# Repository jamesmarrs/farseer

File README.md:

# farseer

In-car race telemetry module: GPS uplink over UDP via Quectel BG95-M3, with a
low-volume server downlink.

## Bench wiring

See [docs/bench-wiring.md](docs/bench-wiring.md) for Curiosity Nano + Sixfab
Cellular IoT HAT connections, power rails, and bring-up checklist.

## Custom board

**The KiCad project is the single source of truth for the circuit** —
schematic, nets, reference designators, values, footprints, and MPNs. Open it
with:

```bash
open ki_cad_project/farseer/farseer.kicad_pro
```

Export the rendered schematic PDF and the BOM CSV (into `docs/generated/`,
machine-generated — never hand-edit) with:

```bash
./scripts/export_kicad.sh
```

The design *rationale* — datasheet citations, sizing math, traps, and
trade-offs the schematic cannot carry — lives in `docs/`, one document per
block: [MCU](docs/mcu-support-circuit.md),
[cellular](docs/cellular-support-circuit.md),
[GNSS](docs/gnss-support-circuit.md),
[power](docs/power-support-circuit.md), and
[interconnect](docs/interconnect-and-pin-budget.md) where the pin budget is
reconciled against the 48-pin PPS tables. Off-board parts (antennas, pigtail,
SIM) and cost estimates are in [docs/procurement.md](docs/procurement.md).
Pre-KiCad drawings and BOMs are retained in `docs/_archive/` for history only
and must not be treated as authoritative.

It carries no on-board debugger, so the Curiosity Nano's one-cable-does-everything
arrangement splits in two:

| | Bench (Curiosity Nano) | Custom board |
|---|---|---|
| Program + debug | Micro-USB to the on-board ATSAMD21 | **PICkit 5** on `J_icsp`, a 6-pin ICSP header |
| 115200 console | Same cable, debugger's CDC | **USB-C** on `J_dbg`, via a CP2102N bridge |

USB on the custom board is **data only** — it never powers the board, and the
PICkit must not be asked to power the target either.

## Server UDP tunnel (LocalXpose)

The module sends its telemetry datagrams over UDP to `BG95_SERVER_HOST` /
`BG95_SERVER_PORT` (defined in `bg95.h`). During development that destination is
a [LocalXpose](https://localxpose.io/) (`loclx`) UDP tunnel that forwards public
traffic to a listener on the dev machine.

### One-time setup

```bash
loclx account login                       # authenticate (UDP forwarding needs a paid plan)
loclx endpoint reserve --port 59128 --region us   # reserve us.loclx.io:59128 (once)
```

### Run the tunnel

Start the tunnel BEFORE powering the module, and forward to the same port your
server binds:

```bash
loclx tunnel udp --reserved-endpoint us.loclx.io:59128 --to 127.0.0.1:9000
```

### Gotchas (learned the hard way)

- **Use `127.0.0.1`, never `localhost`, in `--to`.** With `--to localhost:9000`
  loclx does not forward: `localhost` can resolve to IPv6 `::1` while the server
  binds IPv4, so tunneled packets are silently dropped even though the tunnel
  shows "running". Always use the IP literal, e.g. `--to 127.0.0.1:9000`.
- **Keep the port in sync.** The reserved-endpoint port, the module's
  `BG95_SERVER_PORT` in `bg95.h`, and your server's bind port (the `--to` port)
  must all agree. The reserved endpoint's public port and the local `--to` port
  do NOT have to match each other, but the module must target the public port.
- **`--to` port must match the server's bind port**, and the server must listen
  on that UDP port (e.g. `nc -u -l 9000` for a quick stand-in).
- **UDP forwarding is a paid `loclx` feature.** On a free plan the tunnel can
  appear up but never forward UDP.
- **`SEND OK` from the BG95 only means the module handed the datagram to the
  network** — UDP has no delivery ack, so it does not confirm the server (or
  tunnel) received anything.

### Verify the public path

Independently of the module, send a probe to the public endpoint and watch the
server (or a `nc -u -l <port>` stand-in) for it:

```bash
echo "probe" | nc -u -w1 us.loclx.io 59128
```

If the probe lands, the tunnel is good and any remaining delivery gap is on the
module egress side (e.g. BG95 DNS resolution of the host). If it does not land,
the tunnel/endpoint/port/plan is the problem — no firmware change will help.

## Structure

| Path                       | Purpose                                                                                                                             |
|----------------------------|-------------------------------------------------------------------------------------------------------------------------------------|
| _build                     | The [CMake build tree](https://cmake.org/cmake/help/latest/manual/cmake.1.html#introduction-to-cmake-buildsystems), can be deleted. |
| cmake                      | Generated [CMake](https://cmake.org/) files. May be deleted if user.cmake has not been added                                        |
| .vscode                    | See [VSCode](https://code.visualstudio.com/docs/getstarted/settings)                                                                |
| .vscode/settings.json      | Workspace specific settings                                                                                                         |
| .vscode/farseer.mplab.json | The MPLAB project file, should not be deleted                                                                                       |
| out                        | Final build artifacts                                                                                                               |

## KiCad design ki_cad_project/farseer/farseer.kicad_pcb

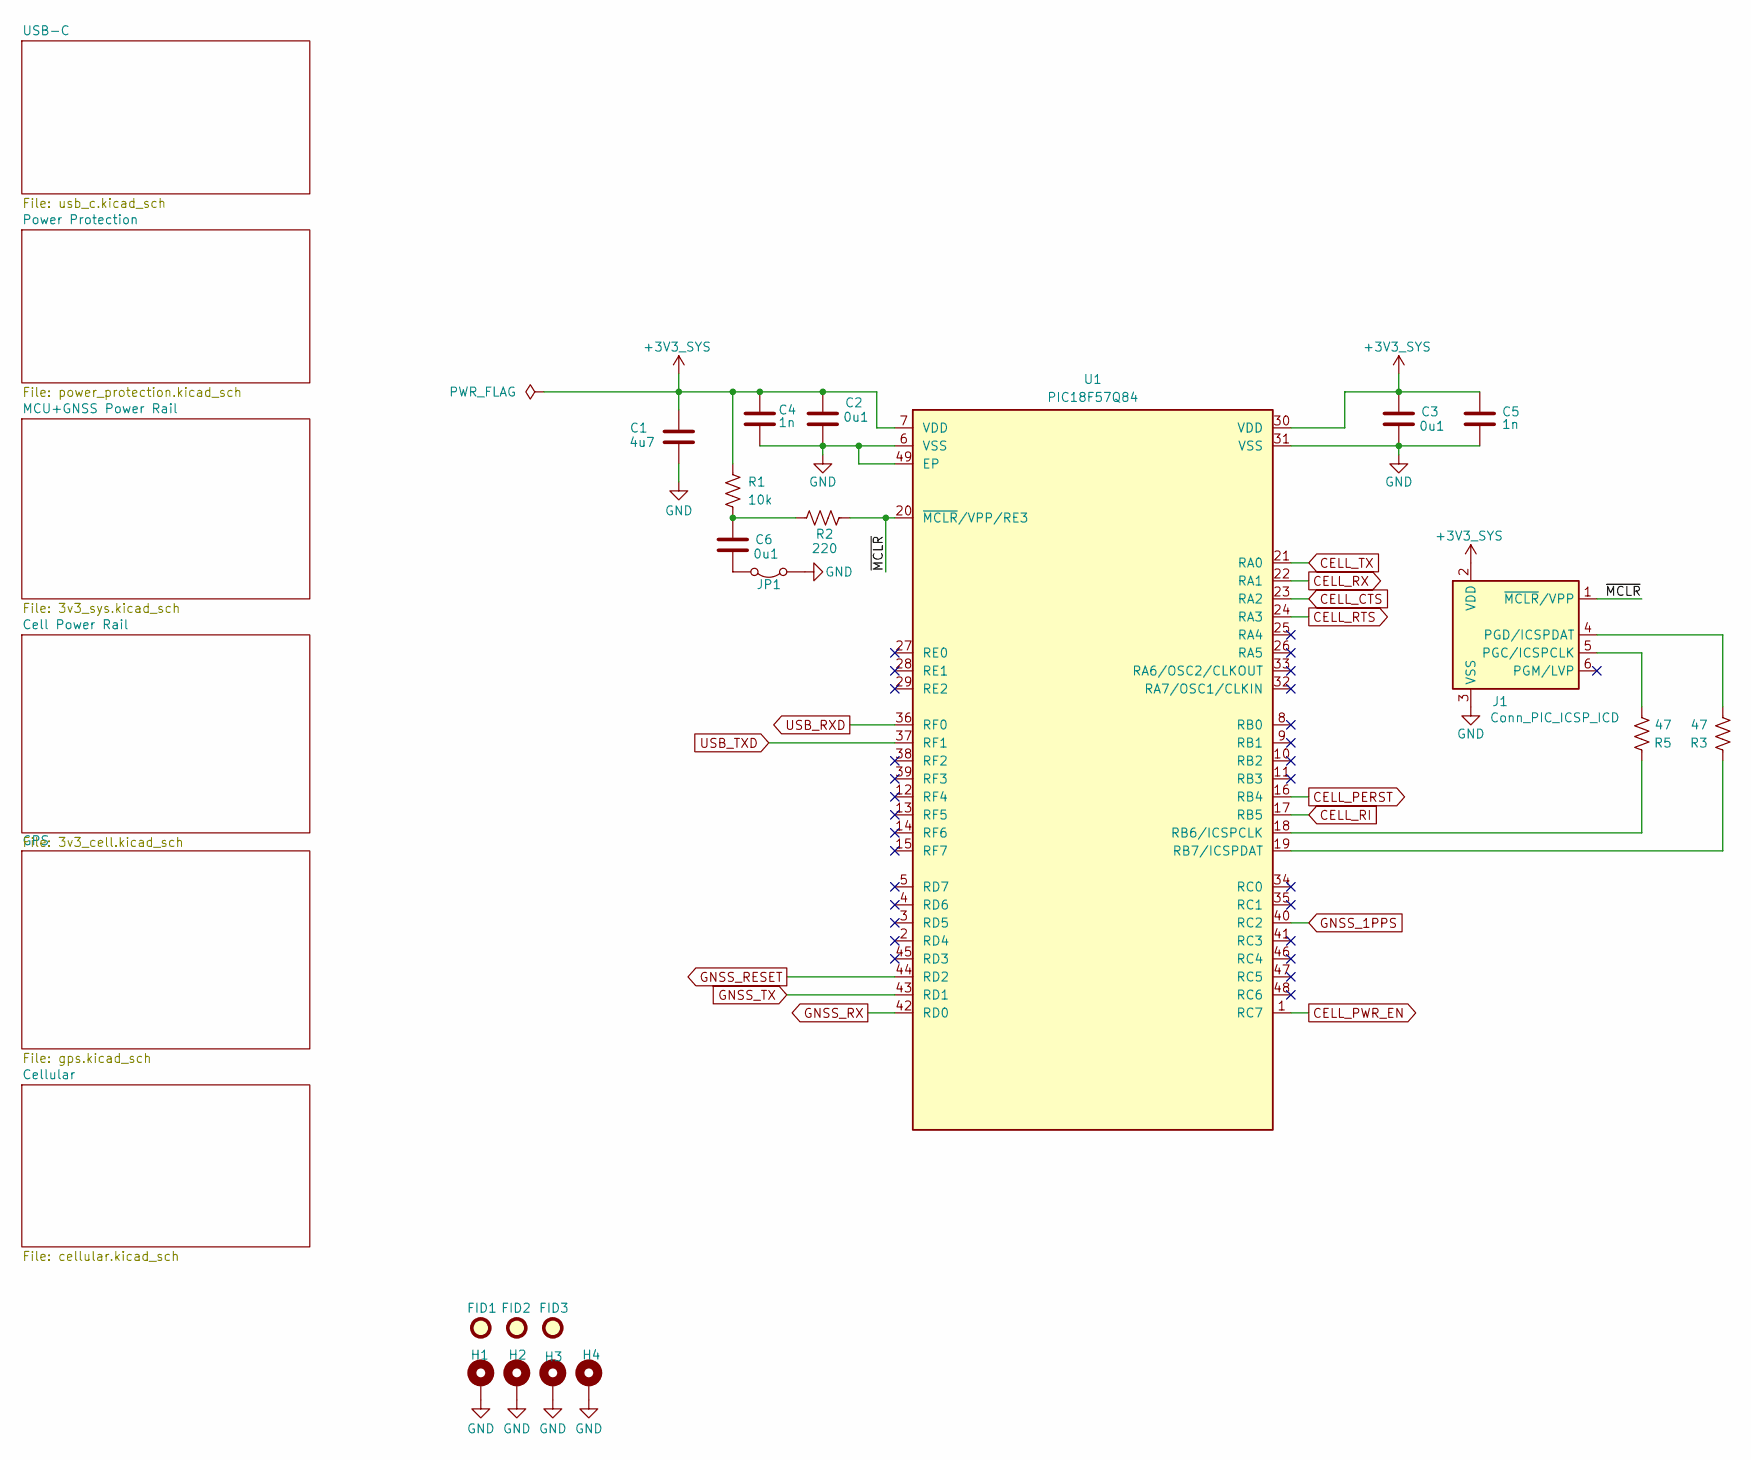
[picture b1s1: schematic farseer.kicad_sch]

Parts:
C1: 4u7; C_0805_2012Metric; MPN GCM21BR71C475KA73L
C2, C3, C6: 0u1; C_0402_1005Metric; MPN GCM155R71E104KE02D
C4, C5: 1n; C_0402_1005Metric; MPN GCM155R71H102KA37D
FID1, FID2, FID3: Fiducial; Fiducial_1mm_Mask2mm
H1, H2, H3, H4: MountingHole; MountingHole_3.2mm_M3_Pad_Via
J1: Conn_PIC_ICSP_ICD; PinHeader_1x06_P2.54mm_Vertical; MPN 61300611021
JP1: PinHeader_1x02_P2.54mm_Vertical; MPN 61300211121
R1: 10k; R_0603_1608Metric; MPN AC0603FR-0710KL
R2: 220; R_0603_1608Metric; MPN AC0603FR-07220RL
R3, R5: 47; R_0603_1608Metric; MPN AC0603FR-0747RL
U1: PIC18F57Q84; TQFP-48-1EP_7x7mm_P0.5mm_EP3.5x3.5mm_ThermalVias; MPN PIC18F57Q84-I/PT; DigikeyPN 150-PIC18F57Q84-I/PT-ND

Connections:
+3V3_SYS: C1.2, C2.1, C3.1, C4.1, C5.1, J1.2 (VDD), R1.1, U1.7 (VDD), U1.30 (VDD); also elsewhere on the board
/~MCLR: J1.1 (~MCLR/VPP), R2.2, U1.20 (~MCLR/VPP/RE3)
CELL_CTS: U1.23 (RA2); also elsewhere on the board
CELL_PERST: U1.16 (RB4); also elsewhere on the board
CELL_PWR_EN: U1.1 (RC7); also elsewhere on the board
CELL_RI: U1.17 (RB5); also elsewhere on the board
CELL_RTS: U1.24 (RA3); also elsewhere on the board
CELL_RX: U1.22 (RA1); also elsewhere on the board
CELL_TX: U1.21 (RA0); also elsewhere on the board
GND: C1.1, C2.2, C3.2, C4.2, C5.2, H1.1 (1_1), H2.1 (1_1), H3.1 (1_1), H4.1 (1_1), J1.3 (VSS), JP1.2 (B), U1.6 (VSS), U1.31 (VSS), U1.49 (EP); also elsewhere on the board
GNSS_1PPS: U1.40 (RC2); also elsewhere on the board
GNSS_RESET: U1.44 (RD2); also elsewhere on the board
GNSS_RX: U1.42 (RD0); also elsewhere on the board
GNSS_TX: U1.43 (RD1); also elsewhere on the board
unnamed: C6.1, R1.2, R2.1
unnamed: J1.5 (PGC/ICSPCLK), R5.2
unnamed: J1.4 (PGD/ICSPDAT), R3.2
unnamed: C6.2, JP1.1 (A)
unnamed: R5.1, U1.18 (RB6/ICSPCLK)
unnamed: R3.1, U1.19 (RB7/ICSPDAT)
USB_RXD: U1.36 (RF0); also elsewhere on the board
USB_TXD: U1.37 (RF1); also elsewhere on the board

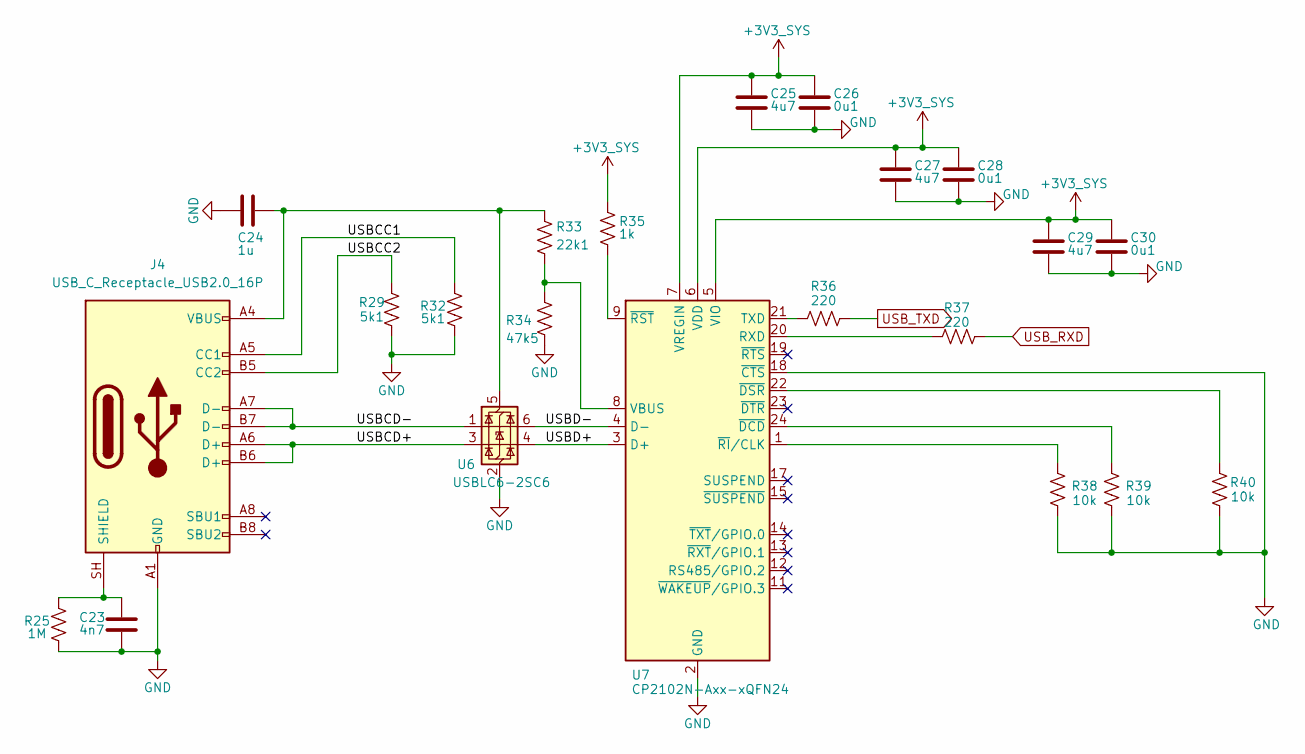
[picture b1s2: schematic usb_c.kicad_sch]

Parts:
C23: 4n7; C_1206_3216Metric; MPN C1206C472KGRACAUTO
C24: 1u; C_0402_1005Metric; MPN GCM155R71C105KA55D
C25, C27, C29: 4u7; C_0603_1608Metric; MPN GRT188C71C475KE13D
C26, C28, C30: 0u1; C_0402_1005Metric; MPN GCM155R71E104KE02D
J4: USB_C_Receptacle_USB2.0_16P; USB_C_Receptacle_GCT_USB4105-xx-A_16P_TopMnt_Horizontal; MPN USB4105-GF-A
R25: 1M; R_0603_1608Metric; MPN AC0603FR-071ML
R29, R32: 5k1; R_0603_1608Metric; MPN AC0603FR-075K1L
R33: 22k1; R_0603_1608Metric; MPN AC0603FR-0722K1L
R34: 47k5; R_0603_1608Metric; MPN AC0603FR-0747K5L
R35: 1k; R_0603_1608Metric; MPN AC0603FR-071KL
R36, R37: 220; R_0603_1608Metric; MPN AC0603FR-07220RL
R38, R39, R40: 10k; R_0603_1608Metric; MPN AC0603FR-0710KL
U6: USBLC6-2SC6; SOT-23-6; MPN USBLC6-2SC6Y
U7: CP2102N-Axx-xQFN24; QFN-24-1EP_4x4mm_P0.5mm_EP2.6x2.6mm; MPN CP2102N-A02-GQFN24

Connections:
+3V3_SYS: C25.1, C26.1, C27.1, C28.1, C29.1, C30.1, R35.2, U7.5 (VIO), U7.6 (VDD), U7.7 (VREGIN); also elsewhere on the board
/USB-C/USBCC1: J4.A5 (CC1), R32.2
/USB-C/USBCC2: J4.B5 (CC2), R29.1
/USB-C/USBCD+: J4.A6 (D+), J4.B6 (D+), U6.3 (I/O2)
/USB-C/USBCD-: J4.A7 (D-), J4.B7 (D-), U6.1 (I/O1)
/USB-C/USBD+: U6.4 (I/O2), U7.3 (D+)
/USB-C/USBD-: U6.6 (I/O1), U7.4 (D-)
GND: C23.2, C24.2, C25.2, C26.2, C27.2, C28.2, C29.2, C30.2, J4.A1 (GND), J4.A12 (GND), J4.B1 (GND), J4.B12 (GND), R25.1, R29.2, R32.1, R34.1, R38.1, R39.1, R40.1, U6.2 (GND), U7.2 (GND), U7.18 (~CTS), U7.25 (GND); also elsewhere on the board
unnamed: C23.1, J4.SH (SHIELD), R25.2
unnamed: C24.1, J4.A4 (VBUS), J4.A9 (VBUS), J4.B4 (VBUS), J4.B9 (VBUS), R33.1, U6.5 (VBUS)
unnamed: R37.2, U7.20 (RXD)
unnamed: R36.1, U7.21 (TXD)
unnamed: R33.2, R34.2, U7.8 (VBUS)
unnamed: R39.2, U7.24 (~DCD)
unnamed: R40.2, U7.22 (~DSR)
unnamed: R38.2, U7.1 (~RI/CLK)
unnamed: R35.1, U7.9 (~RST)
USB_RXD: R37.1; also elsewhere on the board
USB_TXD: R36.2; also elsewhere on the board

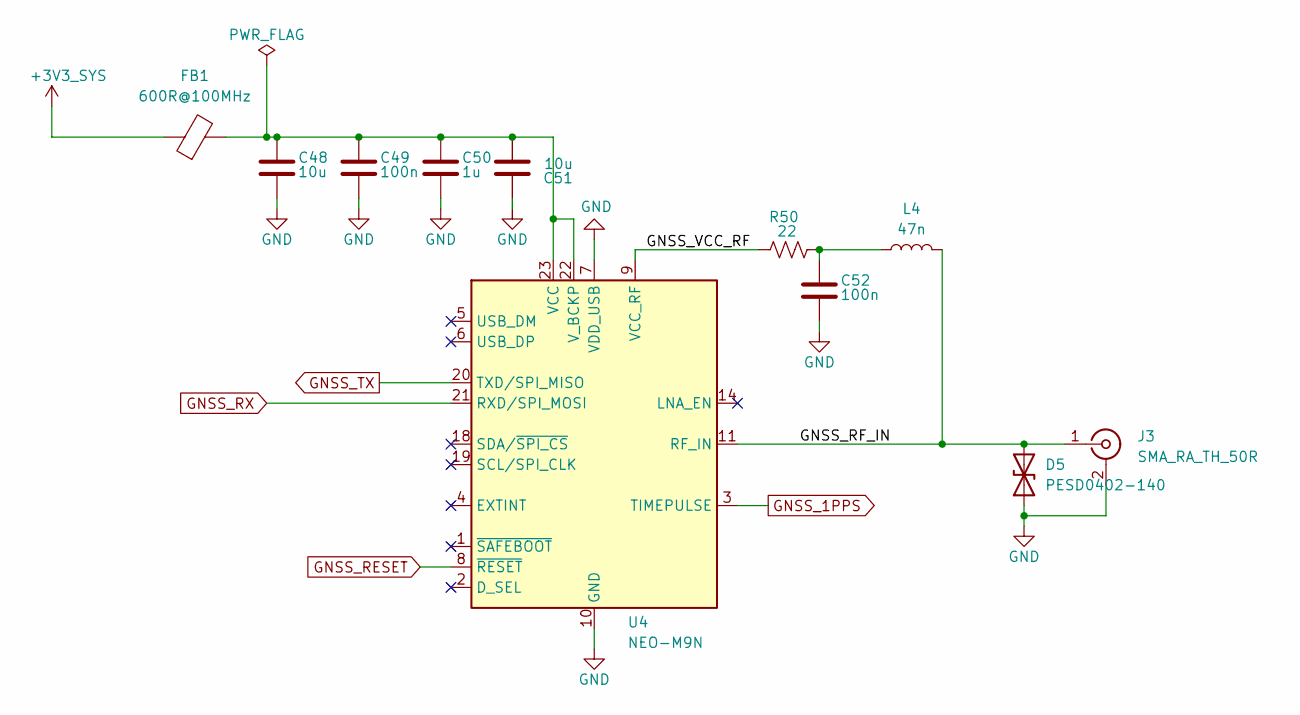
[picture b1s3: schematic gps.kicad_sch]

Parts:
C48, C51: 10u; C_0805_2012Metric; MPN GCM21BR71C106KE22L
C49, C52: 100n; C_0402_1005Metric; MPN GCM155R71C104KA55D
C50: 1u; C_0603_1608Metric; MPN GCM188R71C105KA64D
D5: PESD0402-140; D_0402_1005Metric_PESD0402-140; MPN PESD0402-140
FB1: 600R@100MHz; L_0603_1608Metric; MPN BLM18KG601SZ1D
J3: SMA_RA_TH_50R; SMA_Amphenol_901-143_Horizontal; MPN 132136; DigikeyPN ACX1232-ND
L4: 47n; L_0603_1608Metric; MPN LQW18AN47NG00D
R50: 22; R_0805_2012Metric; MPN ERJ-P06J220V
U4: NEO-M9N; ublox_NEO-M9N-00B; MPN NEO-M9N-00B

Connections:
+3V3_SYS: FB1.1; also elsewhere on the board
/GPS/GNSS_RF_IN: D5.2 (A2), J3.1 (In), L4.2, U4.11 (RF_IN)
/GPS/GNSS_VCC_RF: R50.1, U4.9 (VCC_RF)
GND: C48.2, C49.2, C50.2, C51.1, C52.2, D5.1 (A1), J3.2 (Ext), U4.7 (VDD_USB), U4.10 (GND), U4.12 (GND), U4.13 (GND), U4.24 (GND); also elsewhere on the board
GNSS_1PPS: U4.3 (TIMEPULSE); also elsewhere on the board
GNSS_RESET: U4.8 (~RESET); also elsewhere on the board
GNSS_RX: U4.21 (RXD/SPI_MOSI); also elsewhere on the board
GNSS_TX: U4.20 (TXD/SPI_MISO); also elsewhere on the board
unnamed: C52.1, L4.1, R50.2
unnamed: C48.1, C49.1, C50.1, C51.2, FB1.2, U4.22 (V_BCKP), U4.23 (VCC)

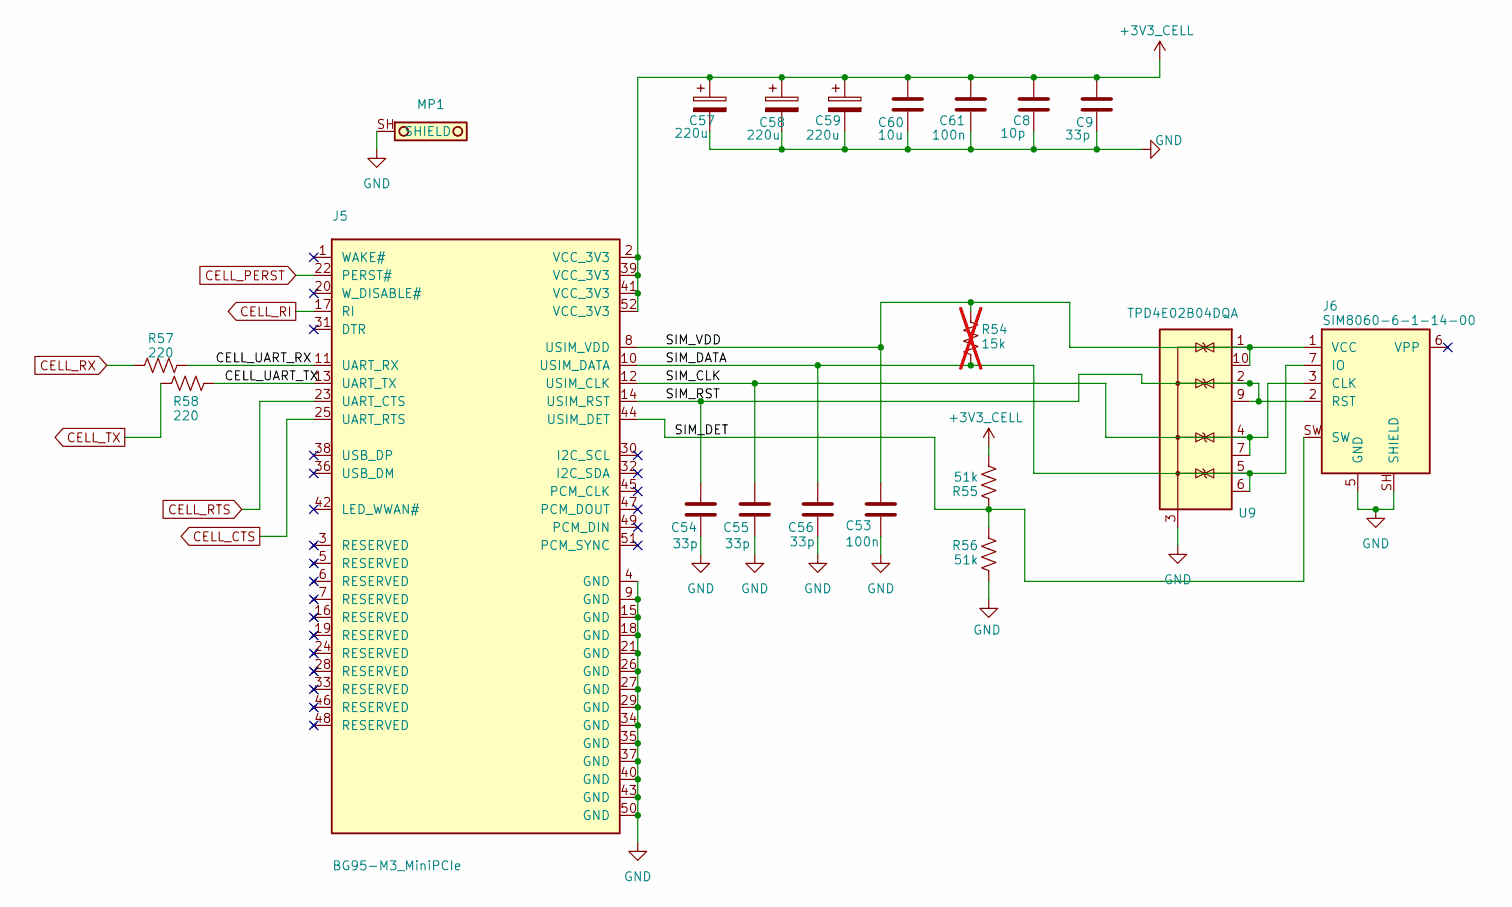
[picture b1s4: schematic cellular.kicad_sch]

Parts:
C8: 10p; C_0402_1005Metric; MPN GCM1555C1H100JA16D
C9, C54, C55, C56: 33p; C_0402_1005Metric; MPN GCM1555C1H330JA16D
C53, C61: 100n; C_0402_1005Metric; MPN GCM155R71C104KA55D
C57, C58, C59: 220u; CP_EIA-7343-31_Kemet-D; MPN T525D227M006ATE025
C60: 10u; C_0805_2012Metric; MPN GCM21BR71C106KE22L
J5: BG95-M3_MiniPCIe; Molex_67910-5700_MiniPCIe; MPN 679105700
J6: SIM8060-6-1-14-00; nanoSIM_GCT_SIM8060-6-1-14-00; MPN SIM8060-6-1-14-00-A
MP1: MiniPCIe_Latch; Molex_48099-5701_MiniPCIe_Latch; MPN 48099-5701
R54: 15k; R_0402_1005Metric; MPN AC0402FR-0715KL; not fitted
R55, R56: 51k; R_0402_1005Metric; MPN AC0402FR-0751KL
R57, R58: 220; R_0603_1608Metric; MPN AC0603FR-07220RL
U9: TPD4E02B04DQA; USON-10_2.5x1.0mm_P0.5mm; MPN TPD4E02B04DQAR

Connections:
+3V3_CELL: C8.1, C9.1, C57.1, C58.1, C59.1, C60.1, C61.1, J5.2 (VCC_3V3), J5.39 (VCC_3V3), J5.41 (VCC_3V3), J5.52 (VCC_3V3), R55.2; also elsewhere on the board
/Cellular/CELL_UART_RX: J5.11 (UART_RX), R57.2
/Cellular/CELL_UART_TX: J5.13 (UART_TX), R58.2
/Cellular/SIM_CLK: C55.1, J5.12 (USIM_CLK), J6.3 (CLK), U9.4 (IO3), U9.7 (NC)
/Cellular/SIM_DATA: C56.1, J5.10 (USIM_DATA), J6.7 (IO), R54.2, U9.5 (IO4), U9.6 (NC)
/Cellular/SIM_DET: J5.44 (USIM_DET), J6.SW, R55.1, R56.1
/Cellular/SIM_RST: C54.1, J5.14 (USIM_RST), J6.2 (RST), U9.2 (IO2), U9.9 (NC)
/Cellular/SIM_VDD: C53.1, J5.8 (USIM_VDD), J6.1 (VCC), R54.1, U9.1 (IO1), U9.10 (NC)
CELL_CTS: J5.25 (UART_RTS); also elsewhere on the board
CELL_PERST: J5.22 (PERST#); also elsewhere on the board
CELL_RI: J5.17 (RI); also elsewhere on the board
CELL_RTS: J5.23 (UART_CTS); also elsewhere on the board
CELL_RX: R57.1; also elsewhere on the board
CELL_TX: R58.1; also elsewhere on the board
GND: C8.2, C9.2, C53.2, C54.2, C55.2, C56.2, C57.2, C58.2, C59.2, C60.2, C61.2, J5.4 (GND), J5.9 (GND), J5.15 (GND), J5.18 (GND), J5.21 (GND), J5.26 (GND), J5.27 (GND), J5.29 (GND), J5.34 (GND), J5.35 (GND), J5.37 (GND), J5.40 (GND), J5.43 (GND), J5.50 (GND), J6.5 (GND), J6.SH (SHIELD), MP1.SH (SHIELD_SH), R56.2, U9.3 (G), U9.8 (G); also elsewhere on the board

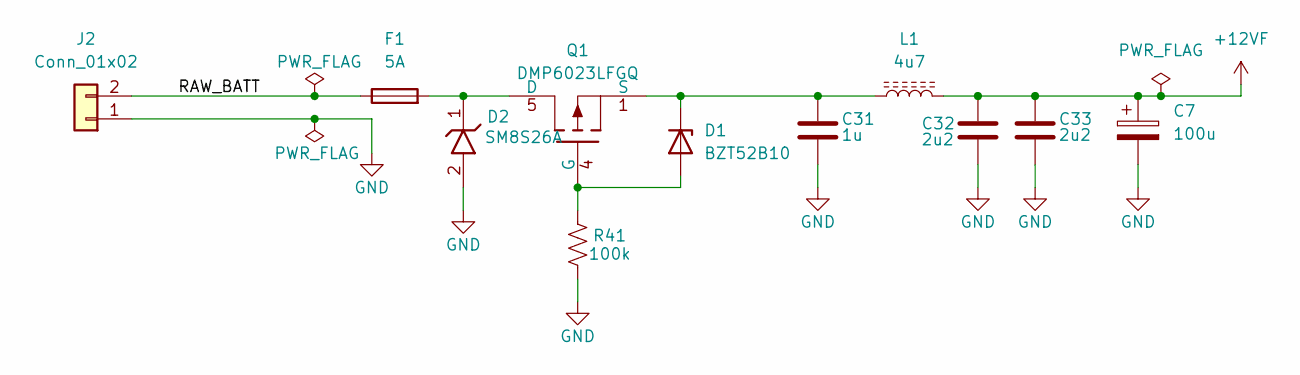
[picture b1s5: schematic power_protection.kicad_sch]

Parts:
C7: 100u; CP_Elec_10x10.5; MPN EEH-ZA1H101P
C31: 1u; C_0805_2012Metric; MPN GCM21BR71H105KA03L
C32, C33: 2u2; C_1206_3216Metric; MPN GCM31CR71H225KA55L
D1: BZT52B10; D_SOD-123F; MPN BZT52B10Q-7
D2: SM8S26A; Littelfuse_DO-218AB; MPN SM8S26A
F1: 5A; Fuseholder_Blade_Mini_Keystone_3568; MPN 0297005.WXNV
J2: Conn_01x02; SolderWire-0.5sqmm_1x02_P4.6mm_D0.9mm_OD2.1mm_Relief
L1: 4u7; L_Bourns_SRN8040TA; MPN SRN8040TA-4R7M
Q1: DMP6023LFGQ; Diodes_PowerDI3333-8; MPN DMP6023LFGQ-13
R41: 100k; R_0603_1608Metric; MPN AC0603FR-07100KL

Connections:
+12VF: C7.1, C32.1, C33.1, L1.2; also elsewhere on the board
/Power Protection/RAW_BATT: F1.1, J2.2
GND: C7.2, C31.2, C32.2, C33.2, D2.2 (A), J2.1, R41.1; also elsewhere on the board
unnamed: D1.2 (A), Q1.4 (G), R41.2
unnamed: C31.1, D1.1 (K), L1.1, Q1.1 (S), Q1.2 (S), Q1.3 (S)
unnamed: D2.1 (K), F1.2, Q1.5 (D)

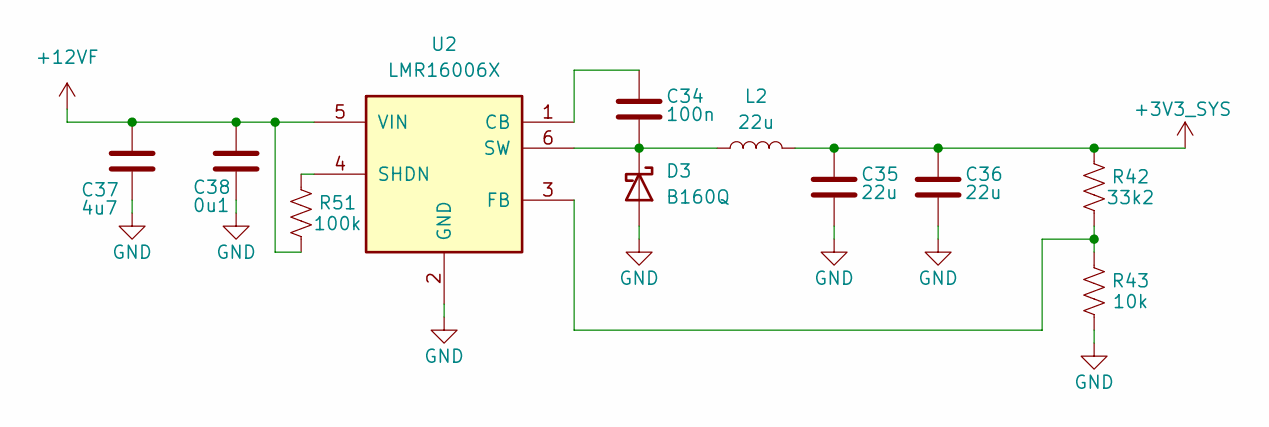
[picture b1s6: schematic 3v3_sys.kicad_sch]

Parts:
C34: 100n; C_0805_2012Metric; MPN GCM21BR71H104KA37L
C35, C36: 22u; C_0805_2012Metric; MPN GCM21BR61A226ME36L
C37: 4u7; C_1210_3225Metric; MPN GCM32ER71H475KA55L
C38: 0u1; C_0805_2012Metric; MPN GCM21BR71H104KA37L
D3: B160Q; D_SMA; MPN B160Q-13-F
L2: 22u; L_Bourns_SRN6045TA; MPN SRN6045TA-220M
R42: 33k2; R_0603_1608Metric; MPN AC0603FR-0733K2L
R43: 10k; R_0603_1608Metric; MPN AC0603FR-0710KL
R51: 100k; R_0603_1608Metric; MPN AC0603FR-07100KL
U2: LMR16006X; TSOT-23-6; MPN LMR16006XDDCR

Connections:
+3V3_SYS: C35.1, C36.1, L2.2, R42.2; also elsewhere on the board
+12VF: C37.1, C38.1, R51.1, U2.5 (VIN); also elsewhere on the board
GND: C35.2, C36.2, C37.2, C38.2, D3.2 (A), R43.1, U2.2 (GND); also elsewhere on the board
unnamed: C34.2, D3.1 (K), L2.1, U2.6 (SW)
unnamed: C34.1, U2.1 (CB)
unnamed: R42.1, R43.2, U2.3 (FB)
unnamed: R51.2, U2.4 (SHDN)

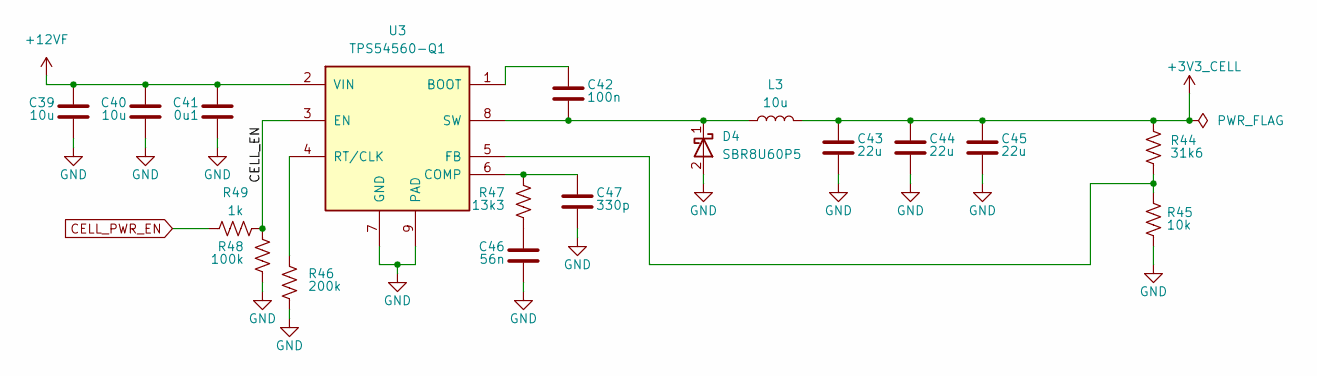
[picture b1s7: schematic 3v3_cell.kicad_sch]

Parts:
C39, C40: 10u; C_1210_3225Metric; MPN GCM32ER71H106KA03L
C41: 0u1; C_0805_2012Metric; MPN GCM21BR71H104KA37L
C42: 100n; C_0805_2012Metric; MPN GCM21BR71H104KA37L
C43, C44, C45: 22u; C_1206_3216Metric; MPN GCM31CR71C226KE02L
C46: 56n; C_0603_1608Metric; MPN GCM188R71H563KA55D
C47: 330p; C_0603_1608Metric; MPN GCM1885C1H331JA16D
D4: SBR8U60P5; D_PowerDI-5_SBR8U60P5; MPN SBR8U60P5-13
L3: 10u; L_Coilcraft_XAL6060-XXX; MPN XAL6060-103MEC
R44: 31k6; R_0603_1608Metric; MPN AC0603FR-0731K6L
R45: 10k; R_0603_1608Metric; MPN AC0603FR-0710KL
R46: 200k; R_0603_1608Metric; MPN AC0603FR-07200KL
R47: 13k3; R_0603_1608Metric; MPN AC0603FR-0713K3L
R48: 100k; R_0603_1608Metric; MPN AC0603FR-07100KL
R49: 1k; R_0603_1608Metric; MPN AC0603FR-071KL
U3: TPS54560-Q1; SOIC-8-1EP_3.9x4.9mm_P1.27mm_EP2.95x4.9mm_Mask2.71x3.4mm_Th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; MPN TPS54560QDDARQ1; DigikeyPN 296-38302-1-ND

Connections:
+3V3_CELL: C43.1, C44.1, C45.1, L3.2, R44.1; also elsewhere on the board
+12VF: C39.1, C40.1, C41.1, U3.2 (VIN); also elsewhere on the board
/Cell Power Rail/CELL_EN: R48.1, R49.2, U3.3 (EN)
CELL_PWR_EN: R49.1; also elsewhere on the board
GND: C39.2, C40.2, C41.2, C43.2, C44.2, C45.2, C46.2, C47.2, D4.2 (A), R45.2, R46.2, R48.2, U3.7 (GND), U3.9 (PAD); also elsewhere on the board
unnamed: C46.1, R47.2
unnamed: C42.2, D4.1 (K), L3.1, U3.8 (SW)
unnamed: C42.1, U3.1 (BOOT)
unnamed: C47.1, R47.1, U3.6 (COMP)
unnamed: R44.2, R45.1, U3.5 (FB)
unnamed: R46.1, U3.4 (RT/CLK)

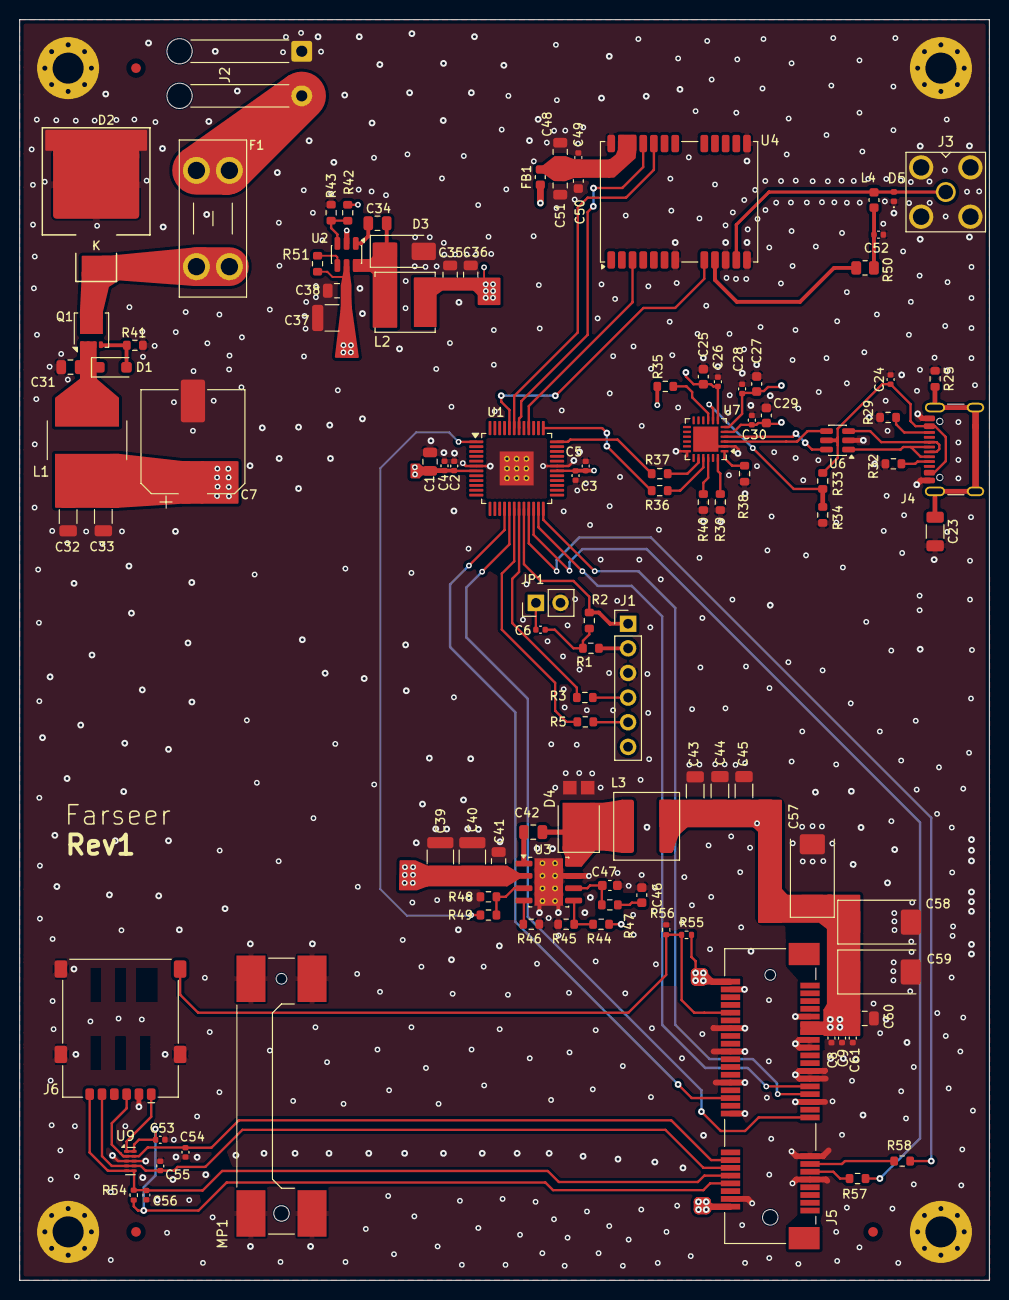
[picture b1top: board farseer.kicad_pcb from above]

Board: 4 copper layers, 100.0 x 130.0 mm, 113 parts (0 on the bottom side), 65 nets.

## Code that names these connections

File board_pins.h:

/**
 * @file board_pins.h
 * @brief Farseer custom-board PIC18F57Q84 pin map (48-pin TQFP).
 *
 * Matches the KiCad schematic (farseer.kicad_sch + child sheets). Net names are
 * peripheral-relative (CELL_RX = card UART_RX, USB_RXD = bridge RXD, etc.).
 * Do not reassign reserved pins below to other functions.
 */
#ifndef BOARD_PINS_H
#define BOARD_PINS_H

/* --- In use by firmware -------------------------------------------------- */
/* RC7  CELL_PWR_EN   out  GPIO     -> U3 (TPS54560-Q1) EN; HIGH = 3V3_CELL on */
/* RF0  USB_RXD       out  U1TX     -> U7 CP2102N RXD (console) */
/* RF1  USB_TXD       in   U1RX     <- U7 CP2102N TXD */
/* RA1  CELL_RX       out  U3TX     -> J5 pin 11 UART_RX (via R57) */
/* RA0  CELL_TX       in   U3RX     <- J5 pin 13 UART_TX (via R58) */
/* RD0  GNSS_RX       out  U2TX     -> U4 NEO-M9N pin 21 RXD */
/* RD1  GNSS_TX       in   U2RX     <- U4 NEO-M9N pin 20 TXD */
/* RB6  ICSPCLK       —    ICSP     -> J1 PGC */
/* RB7  ICSPDAT       —    ICSP     -> J1 PGD */
/* RE3  MCLR          in   reset    -> J1 MCLR / R1 pull-up */

/* --- Wired on PCB, not driven/read by firmware yet — do not reuse -------- */
/* RB4  CELL_PERST    out  GPIO     -> J5 pin 22 PERST# (active-low reset) */
/* RB5  CELL_RI       in   INT2     <- J5 pin 17 RI (wake / URC) */
/* RD2  GNSS_RESET    out  GPIO     -> U4 pin 8 RESET_N (active-low) */
/* RC2  GNSS_1PPS     in   CCP1     <- U4 pin 3 TIMEPULSE */
/* RA2  CELL_CTS      in   U3CTS    <- J5 pin 25 UART_RTS (HW flow control) */
/* RA3  CELL_RTS      out  U3RTS    -> J5 pin 23 UART_CTS (HW flow control) */

/* --- Reserved on schematic, not wired yet -------------------------------- */
/* RB1  (spare)       —    —        reserved for W_DISABLE# if needed later */

#endif /* BOARD_PINS_H */

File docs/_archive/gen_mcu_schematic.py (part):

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SIGNALS = [
    ('RF0', '36', 'DBG_TX', 'to U5 RXD  -  console TX  (U1TX)', AMBER),
    ('RF1', '37', 'DBG_RX', 'from U5 TXD  -  console RX  (U1RX)', AMBER),
    ('RD0', '42', 'GNSS_RX', 'to NEO-M9N pin 21 RXD  (U2TX)', GREEN),
    ('RD1', '43', 'GNSS_TX', 'from NEO-M9N pin 20 TXD  (U2RX)', GREEN),
    ('RB3', '11', 'GNSS_RESET', 'to NEO-M9N pin 8 RESET_N, open-drain', GREEN),
    ('RC2', '40', 'GNSS_1PPS', 'from NEO-M9N pin 3 TIMEPULSE  (CCP1 capture)', GREEN),
    ('RF4', '12', 'CELL_RX', 'to J2 pin 11 UART_RX  (U3TX)', RED),
    ('RF5', '13', 'CELL_TX', 'from J2 pin 13 UART_TX  (U3RX)', RED),
    ('RF6', '14', 'CELL_CTS', 'from J2 pin 25 UART_RTS  (U3CTS, Opt)', RED),
    ('RF7', '15', 'CELL_RTS', 'to J2 pin 23 UART_CTS  (U3RTS, Opt)', RED),
    ('RB0', '8', 'CELL_PERST', 'to J2 pin 22 PERST#, open-drain', RED),
    ('RB1', '9', 'CELL_W_DIS', 'to J2 pin 20 W_DISABLE#  (Opt)', RED),
    ('RB2', '10', 'CELL_RI', 'from J2 pin 17 RI  (INT2, Opt)', RED),
    ('RA2', '23', 'CELL_PWR_EN', 'to buck A EN  -  HIGH = rail on', RED),
    ('RB6', '18', 'ICSPCLK', 'to J_icsp pin 5  -  keep clear of everything else', BLUE),
    ('RB7', '19', 'ICSPDAT', 'to J_icsp pin 4  -  keep clear of everything else', BLUE),
    ('RF3', '39', 'LED0', 'status LED, drives low to light', AMBER),
]
n = len(SIGNALS)
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        elm.IcPin(name='VDD', pin='30', side='left', slot='4/5', anchorname='VDDb'),
        elm.IcPin(name='VSS', pin='6', side='left', slot='3/5'),
        elm.IcPin(name='VSS', pin='31', side='left', slot='2/5', anchorname='VSSb'),
        elm.IcPin(name='MCLR', pin='20', side='left', slot='1/5')]
pins += [elm.IcPin(name=a, pin=p, side='right', slot=f'{n - i}/{n}')
         for i, (a, p, _, _, _) in enumerate(SIGNALS)]

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d += (ms := elm.Resistor().right().at(mnode.center).length(2.6)
      .label(part_lbl('R_mclr2', '220 Ohm'), 'top').color(GREY))
sh.net(ms.end, 'right', 'MCLR_N', BLUE, stub=0.9)
sh.note(ms.end[0] + 3.6, MY + 0.4, 'to U1 pin 20 (RE3 / VPP)', GREY, 'right')

d += (mc := elm.Capacitor().down().at(mnode.center).length(1.7)
      .label(part_lbl('C_mclr', '0.1 uF'), 'left').color(GREY))
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# The two pull-down nodes are staggered in x, and the lower row carries its
# series-R label underneath, so nothing lands on the row above's ground symbol.
for anchor, rref, pdref, net, peer, rlen, rloc in (
        ('PGD', 'R_icsp1', 'R_icspPD1', 'ICSPDAT', 'to U1 RB7, pin 19', 2.2, 'top'),
        ('PGC', 'R_icsp2', 'R_icspPD2', 'ICSPCLK', 'to U1 RB6, pin 18', 4.0, 'bottom')):
    src = getattr(jicsp, anchor)
    d += (r := elm.Resistor().right().at(src).length(rlen)
          .label(part_lbl(rref, '47 Ohm (Opt)'), rloc).color(GREY))
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sh.net(rr.end, 'right', '3V3_SYS', GREEN, stub=1.0,
       note='1 kOhm to VIO - required in all cases', note_x=rr.end[0] + 4.4)

for anchor, ref, net, peer in (('TXD', 'R_dbg1', 'DBG_RX', 'to U1 RF1, pin 37  (U1RX)'),
                               ('RXD', 'R_dbg2', 'DBG_TX', 'from U1 RF0, pin 36  (U1TX)')):
    d += (r := elm.Resistor().right().at(getattr(u5, anchor)).length(2.6)
          .label(part_lbl(ref, '220 Ohm'), 'top').color(GREY))
    sh.net(r.end, 'right', net, AMBER, stub=1.0,
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        'exactly as the Nano wires CDC TX to the target UART RX (DS50003011 Figure 3-1). Do not cross it a second time.\n'
        'Both directions must be populated: RF1 is how a server URL will later be written into the 1 KB Data EEPROM,\n'
        'so an output-only console would foreclose it. No DTR/RTS auto-reset circuit - reset belongs to J_icsp, and an\n'
        'RC on MCLR outside the sheet-3 network would fight the PICkit for the pin. Two SEPARATE 5.1 kOhm CC resistors\n'
        'are required, and D+/D- must reach BOTH A6/A7 and B6/B7 for either cable orientation to work. Route the pair\n'
        'at 90 Ohm differential. No series resistors on D+/D-: the CP2102N integrates the transceiver, its matching,\n'
        'and the pull-ups. Programming is NOT here - the PIC18F57Q84 has no USB peripheral, so U5 is the virtual COM\n'
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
